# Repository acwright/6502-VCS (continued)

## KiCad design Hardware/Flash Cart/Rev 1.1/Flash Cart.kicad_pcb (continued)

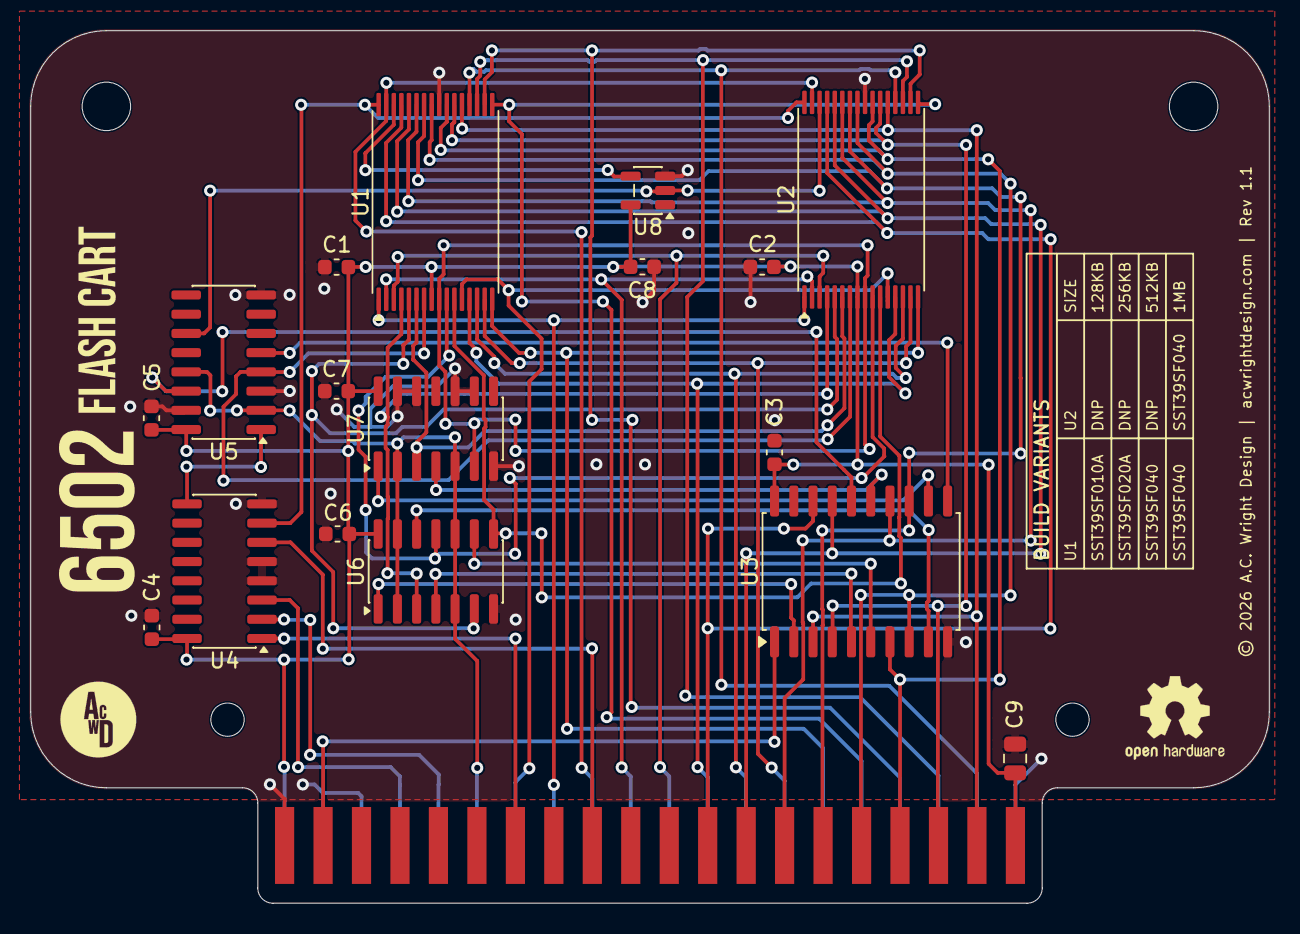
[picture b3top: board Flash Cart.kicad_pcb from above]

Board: 2 copper layers, 81.8 x 57.6 mm, 22 parts (0 on the bottom side), 48 nets.

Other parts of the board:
H1, H2: MountingHole; MountingHole_3.2mm_M3
H3, H4: MountingHole; MountingHole_2.2mm_M2

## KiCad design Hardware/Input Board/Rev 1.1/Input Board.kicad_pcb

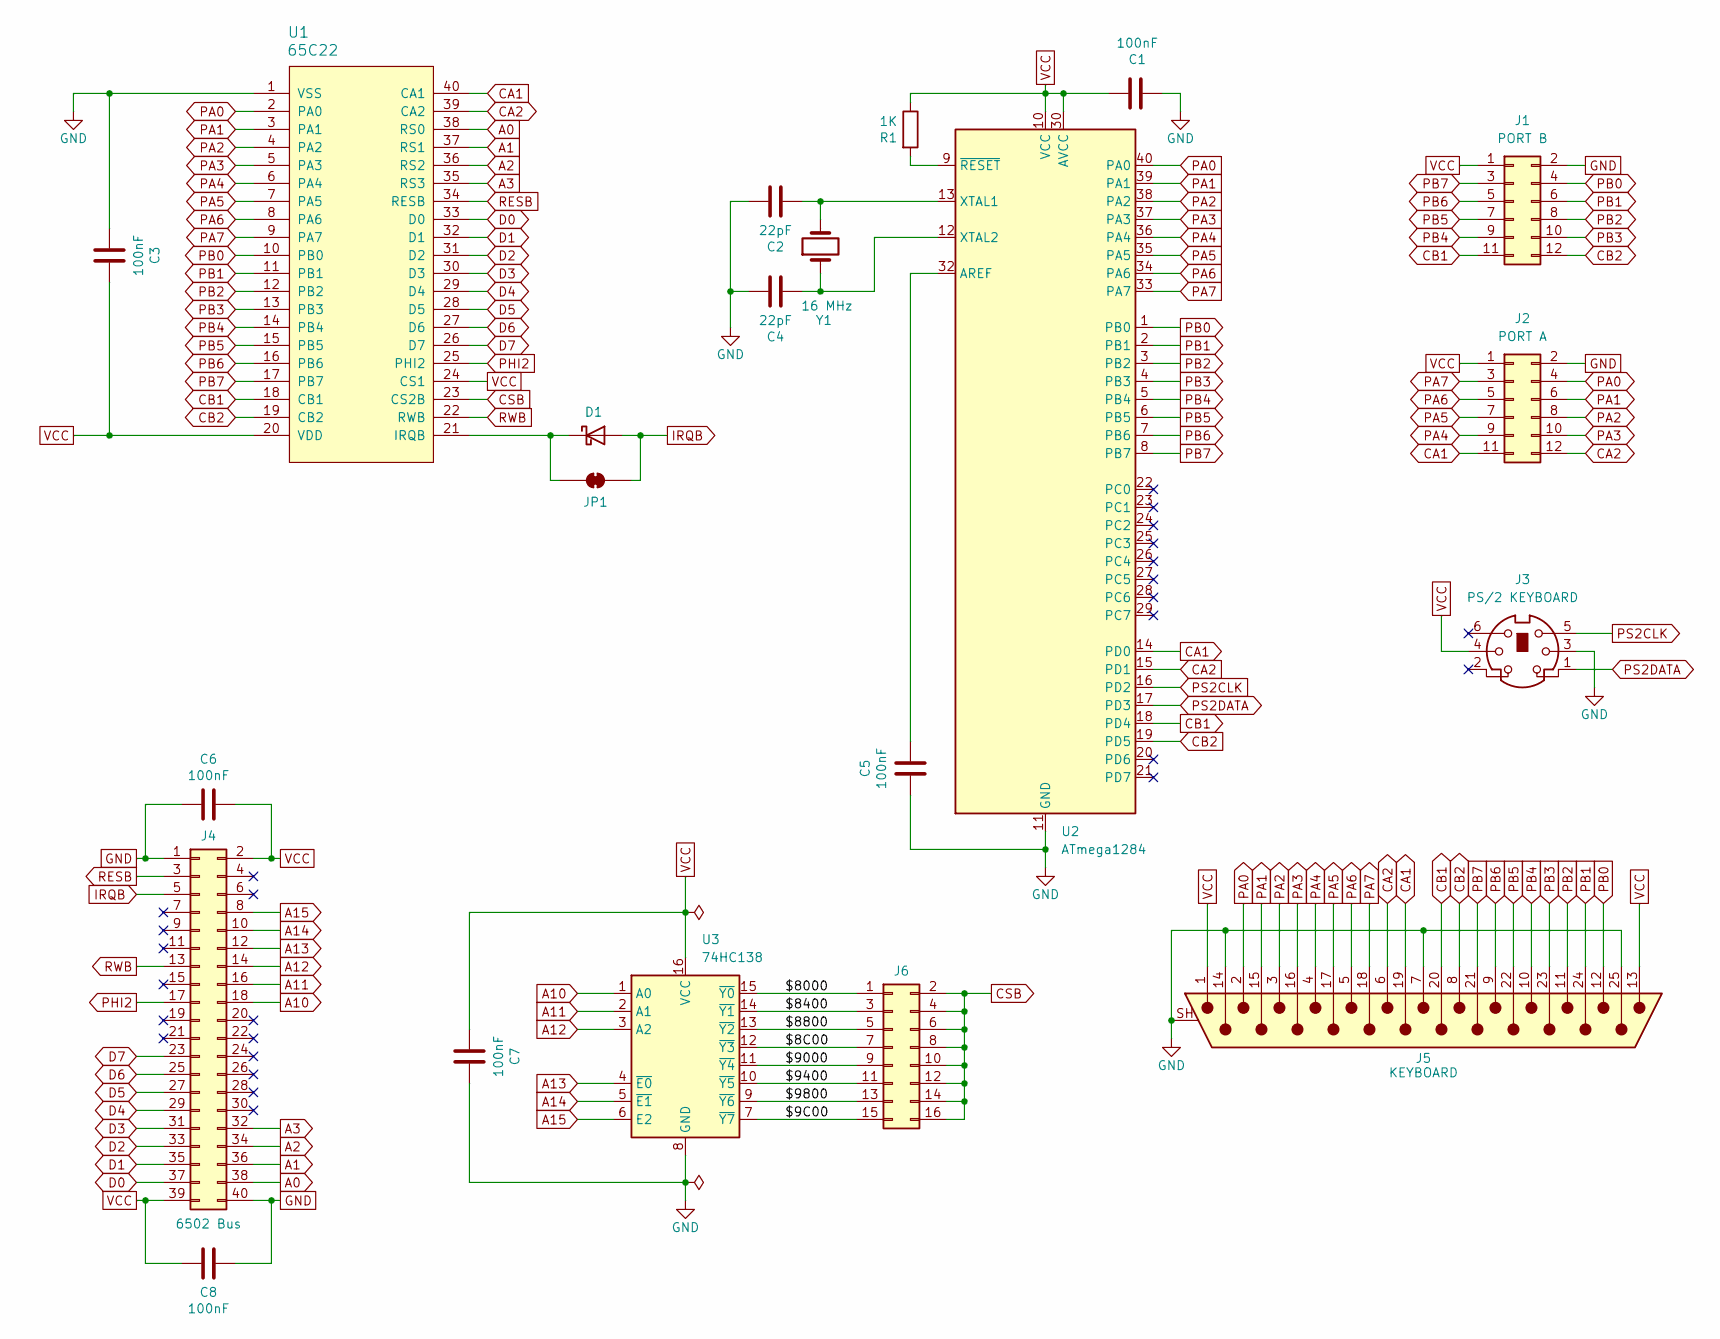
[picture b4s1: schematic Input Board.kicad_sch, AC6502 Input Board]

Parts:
C1, C3, C5, C6, C7, C8: 100nF; C_0805_2012Metric; LCSC C49678
C2, C4: 22pF; C_Disc_D5.0mm_W2.5mm_P2.50mm; Mouser 581-SR151A220JAR
D1: 1N914; D_DO-35_SOD27_P7.62mm_Horizontal; Mouser 512-1N914
J1: PORT B; 6502 GPIO Connector; Mouser 737-BHR-12-VUA
J2: PORT A; 6502 GPIO Connector; Mouser 737-BHR-12-VUA
J3: PS/2 KEYBOARD; PS2 Jack; Mouser 806-KMDGX-6S-BS
J4: 6502 Bus; 6502 Bus Connector; Mouser 710-61204021621
J5: KEYBOARD; DSUB-25_Pins_Horizontal_P2.77x2.84mm_EdgePinOffset7.70mm_Ho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; Digikey 609-1505-ND
J6: IO SELECT; PinHeader_2x08_P2.54mm_Vertical; Mouser 649-67996-140HLF
JP1: IRQ; SolderJumper-2_P1.3mm_Bridged_RoundedPad1.0x1.5mm
R1: 1K; R_0805_2012Metric; LCSC C17513
U1: 65C22; DIP-40_W15.24mm_Socket_LongPads; Mouser 955-W65C22N6TPG-14
U2: ATmega1284; DIP-40_W15.24mm_Socket_LongPads; Mouser 556-ATMEGA1284-PU
U3: 74HC138; SOIC-16_3.9x9.9mm_P1.27mm; LCSC C5602
Y1: 16 MHz; Crystal_HC49-U_Vertical; Digikey X1103-ND

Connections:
/$8C00: J6.7, U3.12 (~Y3)
/$9C00: J6.15, U3.7 (~Y7)
/$8000: J6.1, U3.15 (~Y0)
/$8400: J6.3, U3.14 (~Y1)
/$8800: J6.5, U3.13 (~Y2)
/$9000: J6.9, U3.11 (~Y4)
/$9400: J6.11, U3.10 (~Y5)
/$9800: J6.13, U3.9 (~Y6)
A0: J4.38, U1.38 (RS0)
A1: J4.36, U1.37 (RS1)
A2: J4.34, U1.36 (RS2)
A3: J4.32, U1.35 (RS3)
A10: J4.18, U3.1 (A0)
A11: J4.16, U3.2 (A1)
A12: J4.14, U3.3 (A2)
A13: J4.12, U3.4 (~E0)
A14: J4.10, U3.5 (~E1)
A15: J4.8, U3.6 (E2)
CA1: J2.11, J5.19, U1.40 (CA1), U2.14 (PD0)
CA2: J2.12, J5.6, U1.39 (CA2), U2.15 (PD1)
CB1: J1.11, J5.20, U1.18 (CB1), U2.18 (PD4)
CB2: J1.12, J5.8, U1.19 (CB2), U2.19 (PD5)
CSB: J6.2, J6.4, J6.6, J6.8, J6.10, J6.12, J6.14, J6.16, U1.23 (CS2B)
D0: J4.37, U1.33 (D0)
D1: J4.35, U1.32 (D1)
D2: J4.33, U1.31 (D2)
D3: J4.31, U1.30 (D3)
D4: J4.29, U1.29 (D4)
D5: J4.27, U1.28 (D5)
D6: J4.25, U1.27 (D6)
D7: J4.23, U1.26 (D7)
GND: C1.1, C2.2, C3.1, C4.2, C5.1, C6.2, C7.2, C8.1, J1.2, J2.2, J3.3, J4.1, J4.40, J5.7, J5.14, J5.25, J5.SH (PAD), U1.1 (VSS), U2.11 (GND), U2.31 (GND), U3.8 (GND)
IRQB: D1.2 (A), J4.5, JP1.2 (B)
unnamed: D1.1 (K), JP1.1 (A), U1.21 (IRQB)
unnamed: C5.2, U2.32 (AREF)
unnamed: C2.1, U2.13 (XTAL1), Y1.2
unnamed: C4.1, U2.12 (XTAL2), Y1.1
unnamed: R1.2, U2.9 (~RESET)
PA0: J2.4, J5.2, U1.2 (PA0), U2.40 (PA0)
PA1: J2.6, J5.15, U1.3 (PA1), U2.39 (PA1)
PA2: J2.8, J5.3, U1.4 (PA2), U2.38 (PA2)
PA3: J2.10, J5.16, U1.5 (PA3), U2.37 (PA3)
PA4: J2.9, J5.4, U1.6 (PA4), U2.36 (PA4)
PA5: J2.7, J5.17, U1.7 (PA5), U2.35 (PA5)
PA6: J2.5, J5.5, U1.8 (PA6), U2.34 (PA6)
PA7: J2.3, J5.18, U1.9 (PA7), U2.33 (PA7)
PB0: J1.4, J5.12, U1.10 (PB0), U2.1 (PB0)
PB1: J1.6, J5.24, U1.11 (PB1), U2.2 (PB1)
PB2: J1.8, J5.11, U1.12 (PB2), U2.3 (PB2)
PB3: J1.10, J5.23, U1.13 (PB3), U2.4 (PB3)
PB4: J1.9, J5.10, U1.14 (PB4), U2.5 (PB4)
PB5: J1.7, J5.22, U1.15 (PB5), U2.6 (PB5)
PB6: J1.5, J5.9, U1.16 (PB6), U2.7 (PB6)
PB7: J1.3, J5.21, U1.17 (PB7), U2.8 (PB7)
PHI2: J4.17, U1.25 (PHI2)
PS2CLK: J3.5, U2.16 (PD2)
PS2DATA: J3.1, U2.17 (PD3)
RESB: J4.3, U1.34 (RESB)
RWB: J4.13, U1.22 (RWB)
VCC: C1.2, C3.2, C6.1, C7.1, C8.2, J1.1, J2.1, J3.4, J4.2, J4.39, J5.1, J5.13, R1.1, U1.20 (VDD), U1.24 (CS1), U2.10 (VCC), U2.30 (AVCC), U3.16 (VCC)

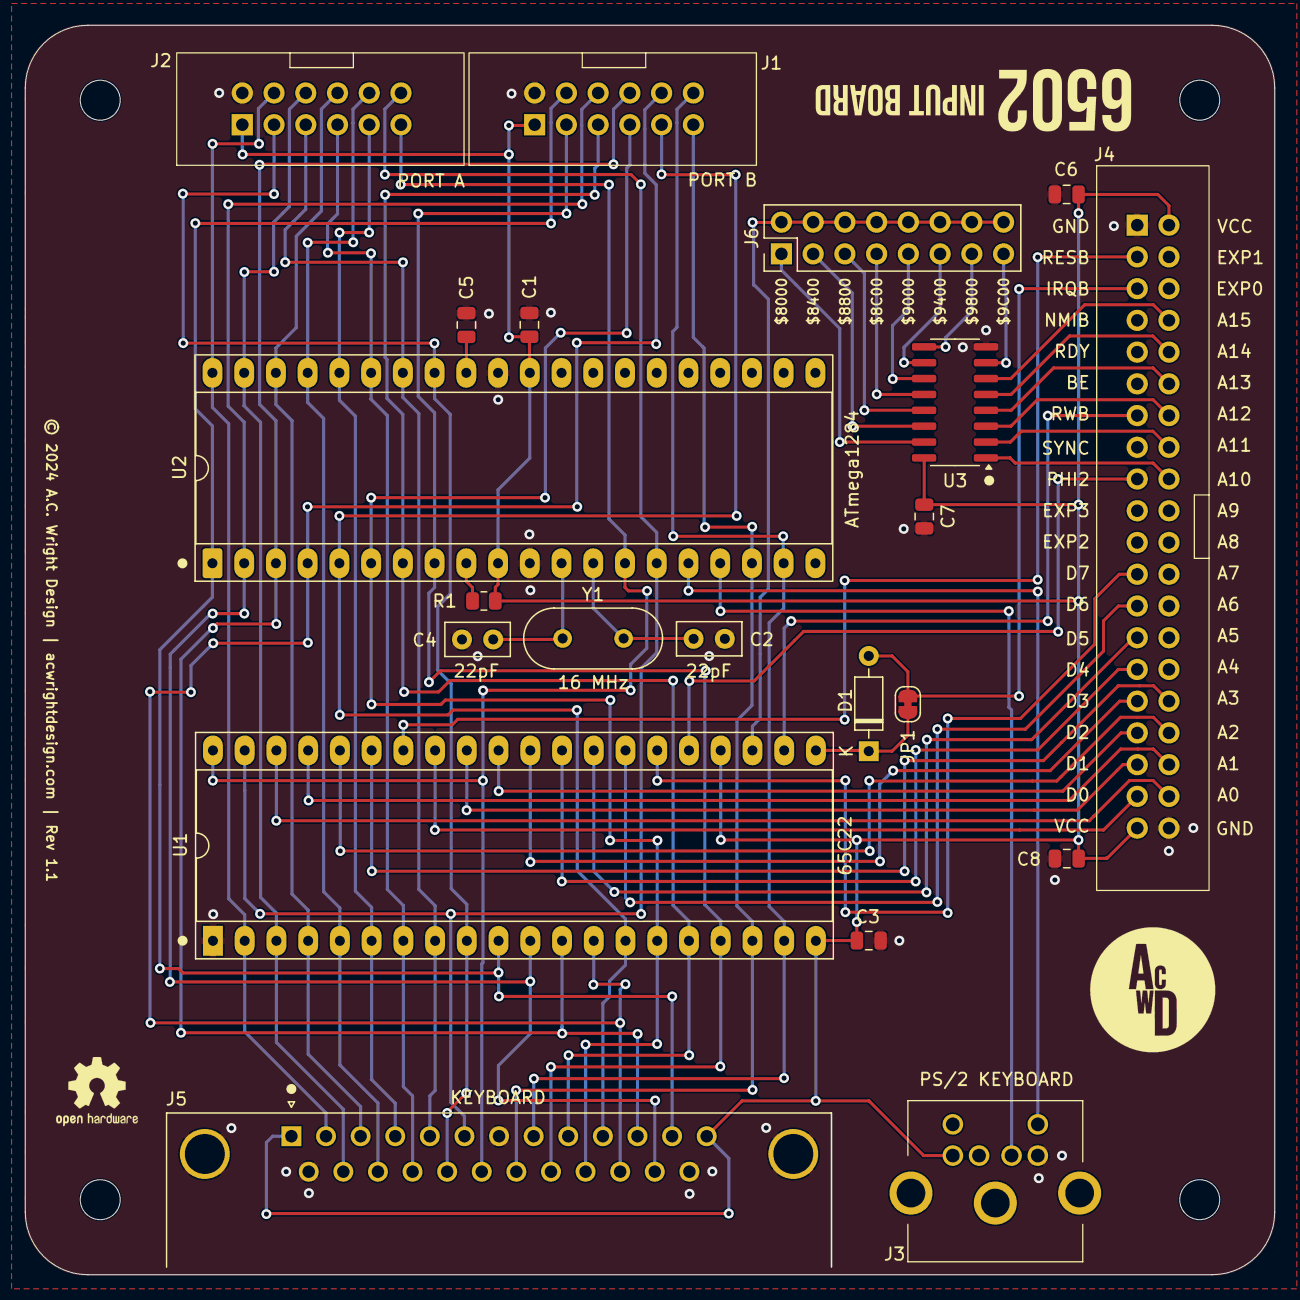
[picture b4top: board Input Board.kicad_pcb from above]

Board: 2 copper layers, 100.0 x 100.0 mm, 25 parts (0 on the bottom side), 60 nets.

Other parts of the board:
H1, H2, H3, H4: MountingHole; MountingHole_3.2mm_M3

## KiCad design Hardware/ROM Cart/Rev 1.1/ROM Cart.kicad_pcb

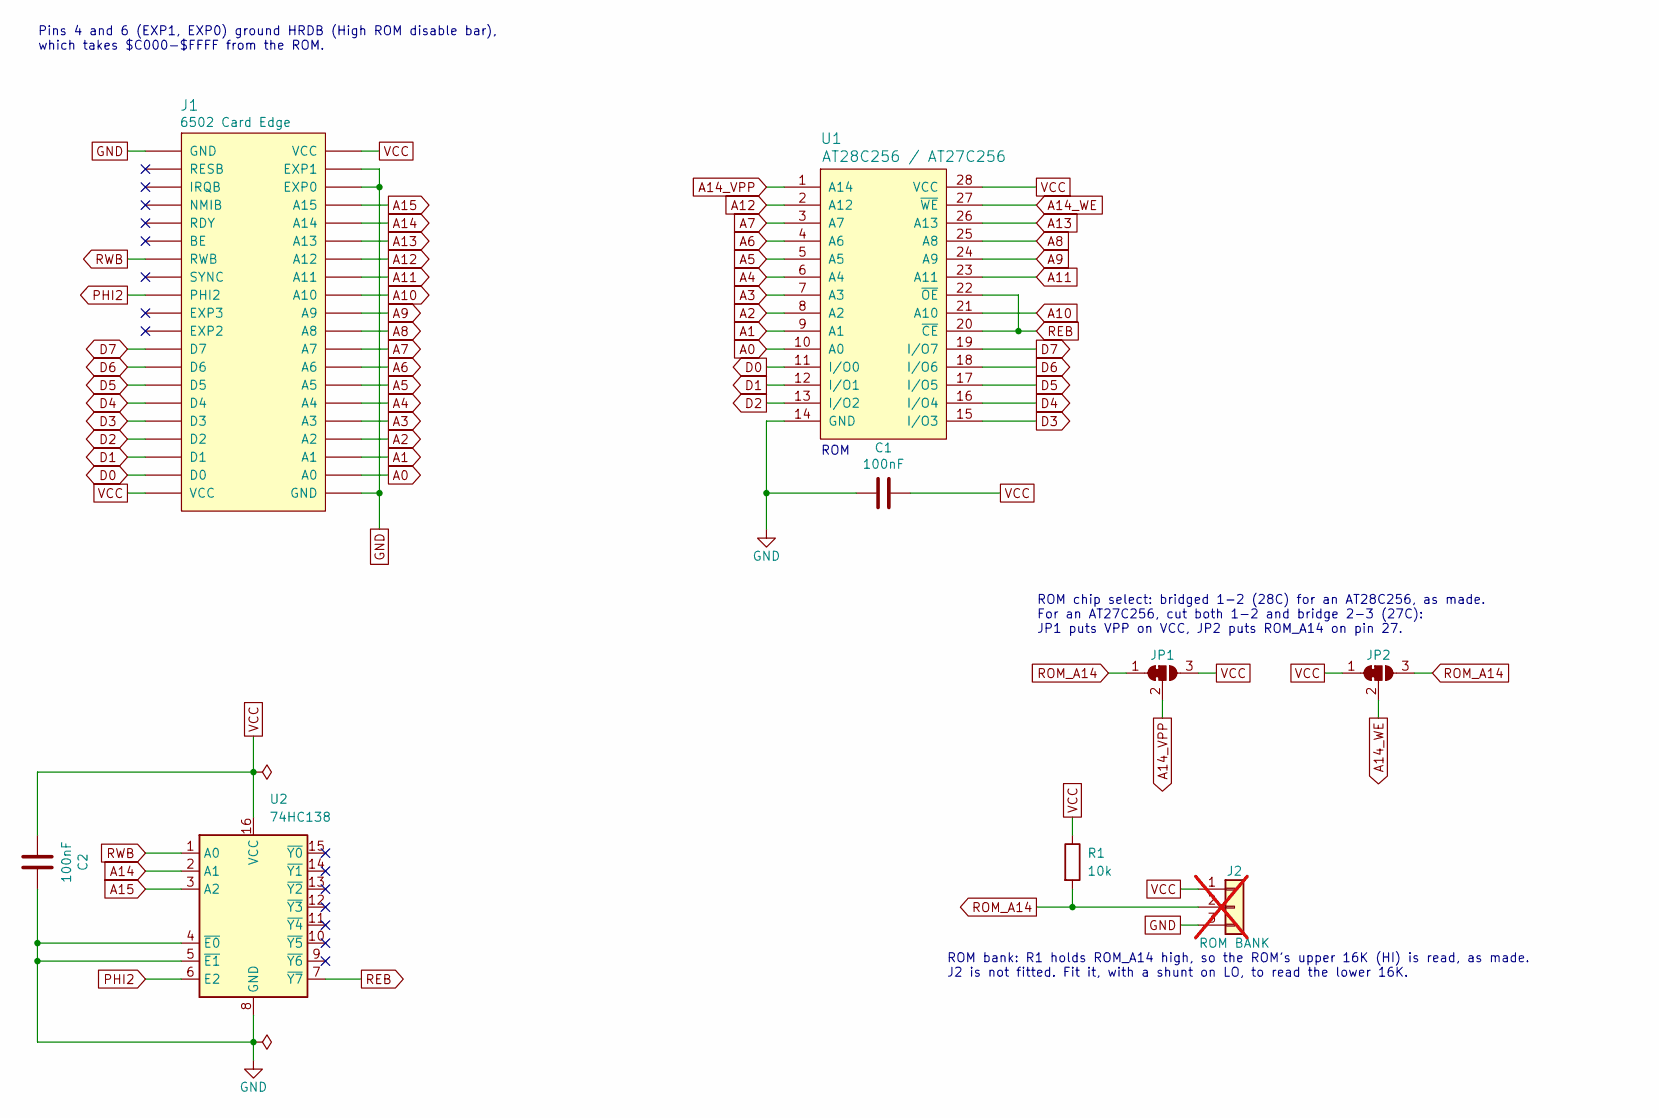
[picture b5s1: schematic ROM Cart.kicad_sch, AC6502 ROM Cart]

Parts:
C1, C2: 100nF; C_Disc_D5.0mm_W2.5mm_P2.50mm; Digikey 478-3187-ND
J1: 6502 Card Edge
J2: ROM BANK; PinHeader_1x03_P2.54mm_Vertical; Digikey S1011EC-40-ND; not fitted
JP1, JP2: SolderJumper_3_Bridged12; SolderJumper-3_P1.3mm_Bridged12_RoundedPad1.0x1.5mm
R1: 10k; R_Axial_DIN0204_L3.6mm_D1.6mm_P5.08mm_Horizontal; Digikey 13-MFR-12FTF52-10KCT-ND
U1: AT28C256 / AT27C256; DIP-28_W15.24mm_Socket_LongPads; Digikey AT28C256-15PU-ND
U2: 74HC138; DIP-16_W7.62mm_Socket_LongPads; Digikey 296-1575-5-ND

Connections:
A0: J1.A0, U1.10 (A0)
A1: J1.A1, U1.9 (A1)
A2: J1.A2, U1.8 (A2)
A3: J1.A3, U1.7 (A3)
A4: J1.A4, U1.6 (A4)
A5: J1.A5, U1.5 (A5)
A6: J1.A6, U1.4 (A6)
A7: J1.A7, U1.3 (A7)
A8: J1.A8, U1.25 (A8)
A9: J1.A9, U1.24 (A9)
A10: J1.A10, U1.21 (A10)
A11: J1.A11, U1.23 (A11)
A12: J1.A12, U1.2 (A12)
A13: J1.A13, U1.26 (A13)
A14: J1.A14, U2.2 (A1)
A14_VPP: JP1.2 (C), U1.1 (A14)
A14_WE: JP2.2 (C), U1.27 (~WE)
A15: J1.A15, U2.3 (A2)
D0: J1.D0, U1.11 (I/O0)
D1: J1.D1, U1.12 (I/O1)
D2: J1.D2, U1.13 (I/O2)
D3: J1.D3, U1.15 (I/O3)
D4: J1.D4, U1.16 (I/O4)
D5: J1.D5, U1.17 (I/O5)
D6: J1.D6, U1.18 (I/O6)
D7: J1.D7, U1.19 (I/O7)
GND: C1.2, C2.2, J1.EXP0, J1.EXP1, J1.GND, J2.3, U1.14 (GND), U2.4 (~E0), U2.5 (~E1), U2.8 (GND)
PHI2: J1.PHI2, U2.6 (E2)
REB: U1.20 (~CE), U1.22 (~OE), U2.7 (~Y7)
ROM_A14: J2.2, JP1.1 (A), JP2.3 (B), R1.2
RWB: J1.RWB, U2.1 (A0)
VCC: C1.1, C2.1, J1.VCC, J2.1, JP1.3 (B), JP2.1 (A), R1.1, U1.28 (VCC), U2.16 (VCC)

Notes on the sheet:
Pins 4 and 6 (EXP1, EXP0) ground HRDB (High ROM disable bar), which takes $C000-$FFFF from the ROM.
ROM bank: R1 holds ROM_A14 high, so the ROM's upper 16K (HI) is read, as made. J2 is not fitted. Fit it, with a shunt on LO, to read the lower 16K.
ROM
ROM chip select: bridged 1-2 (28C) for an AT28C256, as made. For an AT27C256, cut both 1-2 and bridge 2-3 (27C): JP1 puts VPP on VCC, JP2 puts ROM_A14 on pin 27.

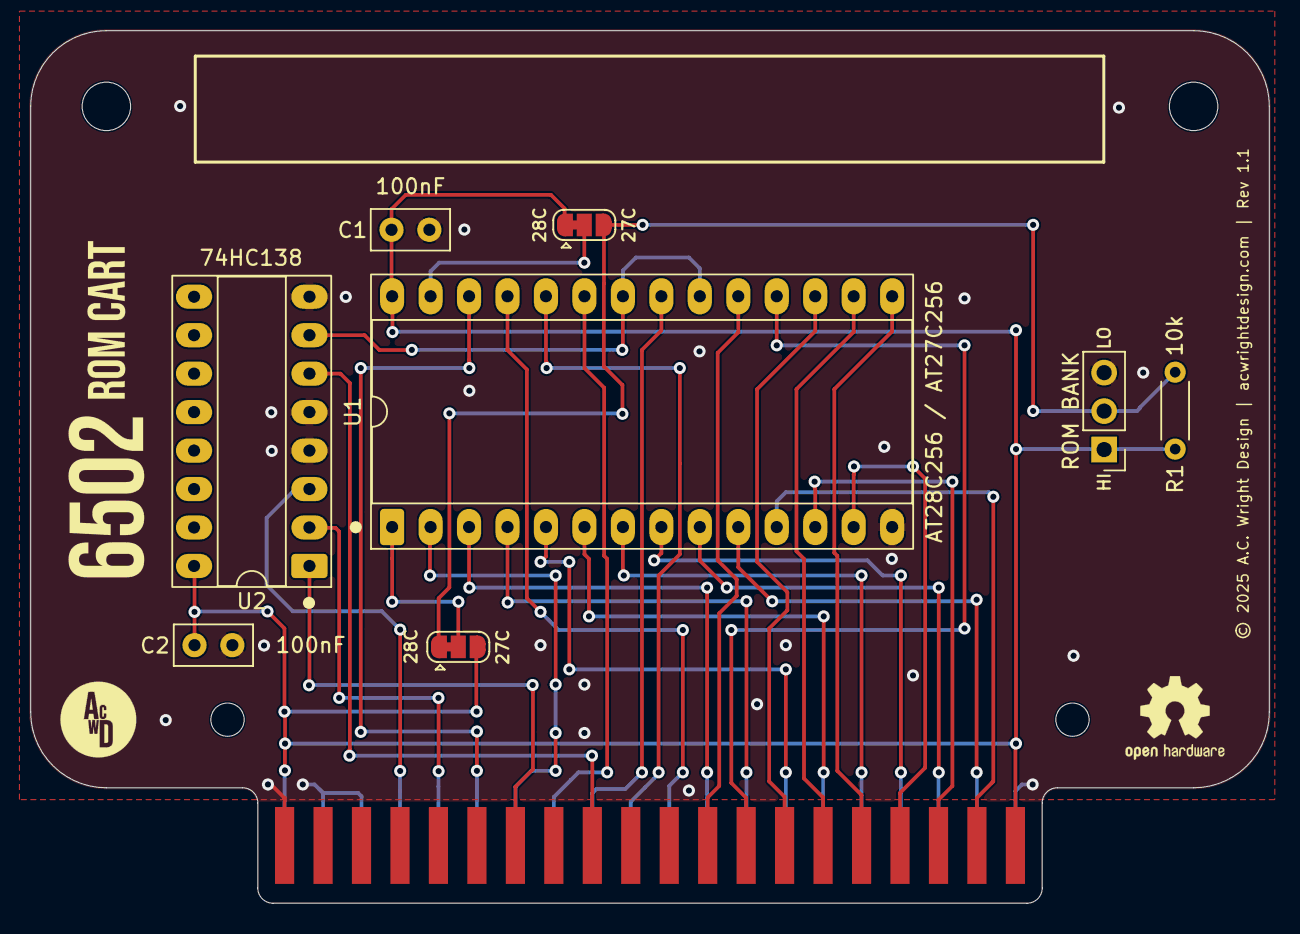
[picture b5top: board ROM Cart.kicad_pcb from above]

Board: 2 copper layers, 81.8 x 57.6 mm, 13 parts (0 on the bottom side), 32 nets.

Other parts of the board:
H1, H2: MountingHole; MountingHole_3.2mm_M3
H3, H4: MountingHole; MountingHole_2.2mm_M2

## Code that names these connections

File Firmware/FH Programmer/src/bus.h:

// The two bus primitives, and nothing above them knows about flash.
//
// The Flash Helper is an Arduino Mega 2560 R3 shield that pretends to be a
// 65C02 on the far side of a cartridge slot (6502-VCS PLAN.md §5).  Everything
// it can do is built out of one read cycle and one write cycle, both of them
// here.
//
// The pin allocation is fixed by the Rev 1.0 schematic.  Three whole ports and
// five single lines, chosen so that the address and the data buses are single
// byte port writes with no bit shuffling:
//
//   PORTA   D22-D29   D0-D7, the data bus          (PA0 = D0)
//   PORTC   D37-D30   A8-A15                       (PC0 = A8; the header runs backwards)
//   PORTL   D49-D42   A0-A7                        (PL0 = A0; likewise)
//   PB7     D13       PHI2                         (also the on-board LED)
//   PB5     D11       RWB
//   PG5     D4        RESB
//   PE4/PE5 D2/D3     IRQB/NMIB - never driven here; they are for the card tester
//
// PLAN.md §5.3 and this project's README both describe the data bus as PORTL.
// That is a slip in the prose: the schematic puts D0-D7 on PORTA and A0-A7 on
// PORTL, and this file follows the schematic.

#pragma once

#include <stdint.h>

/** Take the bus, park it idle, and pulse RESB so the cart's bank register is 0. */
void bus_begin();

/** One write cycle. `addr` is a CPU address; the cart decodes $C000-$FFFF. */
void bus_write(uint16_t addr, uint8_t data);

/** One read cycle. */
uint8_t bus_read(uint16_t addr);

/** Pulse RESB low. This is what clears the cart's bank register to 0. */
void bus_reset_pulse();

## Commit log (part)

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2026-05-03 Cleanup VCS project
2026-05-04 Finish VCS cleanup
2026-05-04 README fix
2026-05-16 Add BOMs
2026-05-19 Finish BOM and add to README
2026-05-19 Restore exclude from BOM
2026-06-15 Change pull up resistor values
2026-06-16 Remove BOM CSV's
2026-06-18 Add Main Board Rev 1.1
